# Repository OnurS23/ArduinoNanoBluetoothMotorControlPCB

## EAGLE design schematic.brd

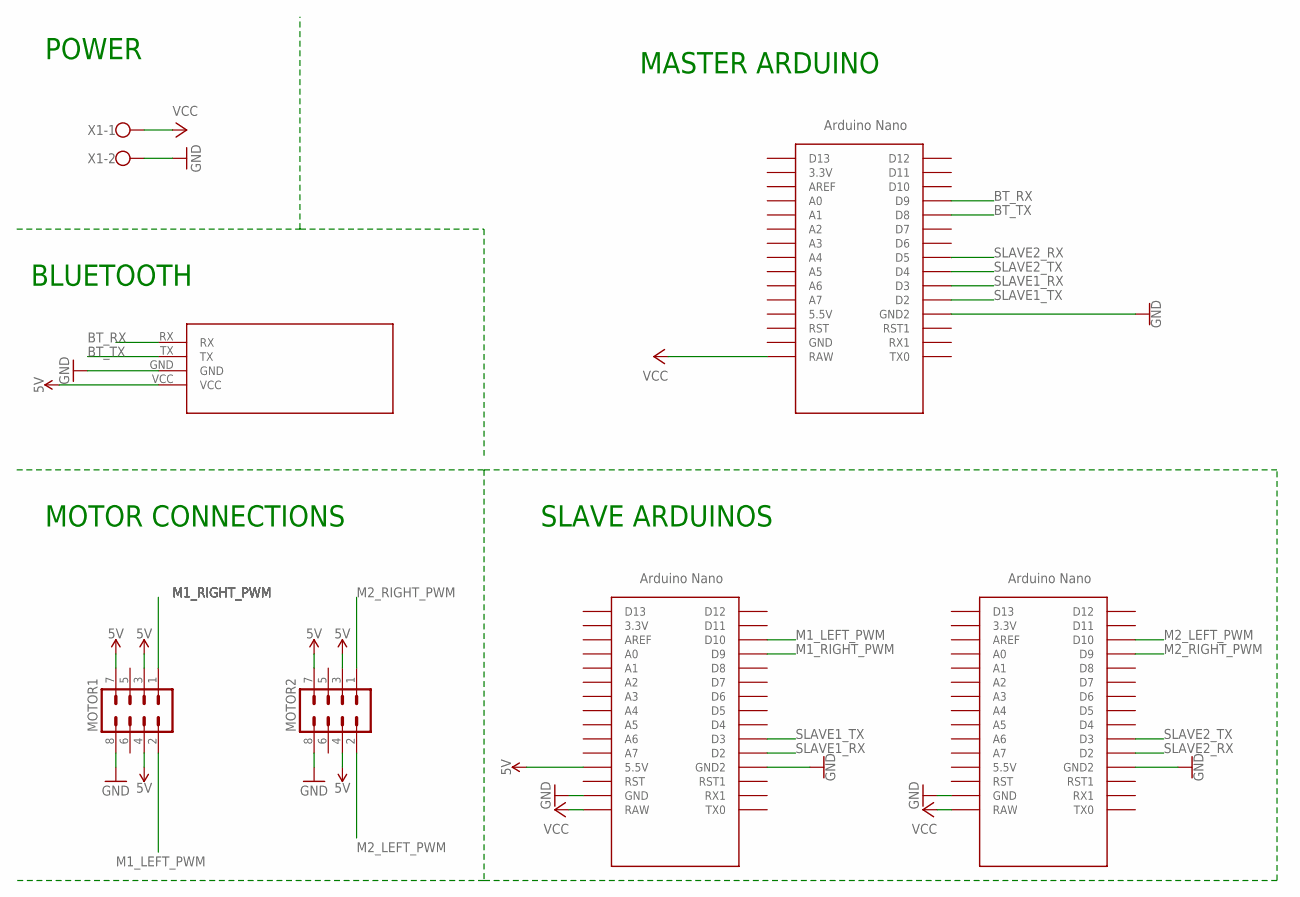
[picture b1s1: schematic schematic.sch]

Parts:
BT: HC06_BLUETOOTH; HC06_BT_FOOTPRıNT
MOTOR1, MOTOR2: MA04-2
U$1, U$2, U$3: NANO
X1: W237-102

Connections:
5V: BT.VCC, MOTOR1.3, MOTOR1.4, MOTOR1.7, MOTOR2.3, MOTOR2.4, MOTOR2.7, U$2.5V (5.5V)
BT_RX: BT.RX, U$1.D9
BT_TX: BT.TX, U$1.D8
GND: BT.GND, MOTOR1.8, MOTOR2.8, U$1.GND1 (GND2), U$2.GND, U$2.GND1 (GND2), U$3.GND, U$3.GND1 (GND2), X1.2
M1_LEFT_PWM: MOTOR1.2, U$2.D10
M1_RIGHT_PWM: MOTOR1.1, U$2.D9
M2_LEFT_PWM: MOTOR2.2, U$3.D10
M2_RIGHT_PWM: MOTOR2.1, U$3.D9
SLAVE1_RX: U$1.D3, U$2.D2
SLAVE1_TX: U$1.D2, U$2.D3
SLAVE2_RX: U$1.D5, U$3.D2
SLAVE2_TX: U$1.D4, U$3.D3
VCC: U$1.RAW, U$2.RAW, U$3.RAW, X1.1

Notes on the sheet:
POWER
BLUETOOTH
MOTOR CONNECTIONS
MASTER ARDUINO
SLAVE ARDUINOS

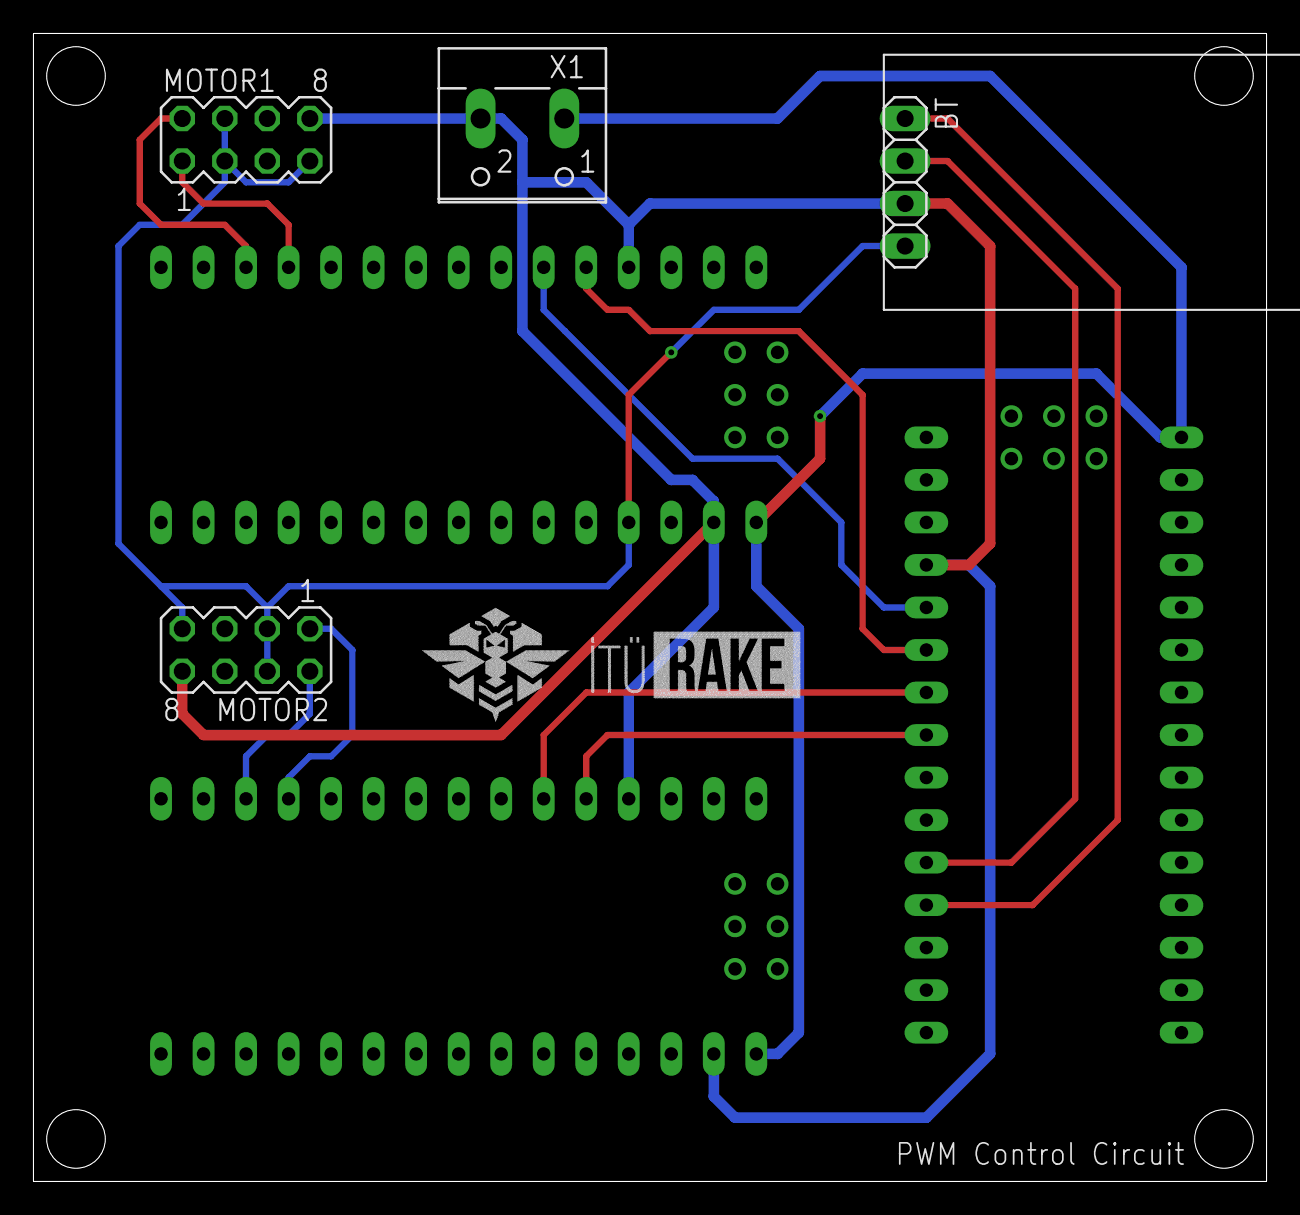
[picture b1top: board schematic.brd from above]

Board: 2 copper layers, 73.7 x 68.6 mm, 7 parts (0 on the bottom side), 13 nets.

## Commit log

2021-11-09 Improved schematic file
2021-11-15 edit
2021-11-17 Board updated
2021-11-17 Trace updated
2021-11-29 Changes for production

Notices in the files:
parts and their libraries:
SparkFun-Aesthetics: Licensing: Creative Commons ShareAlike 4.0 International - https://creativecommons.org/licenses/by-sa/4.0
